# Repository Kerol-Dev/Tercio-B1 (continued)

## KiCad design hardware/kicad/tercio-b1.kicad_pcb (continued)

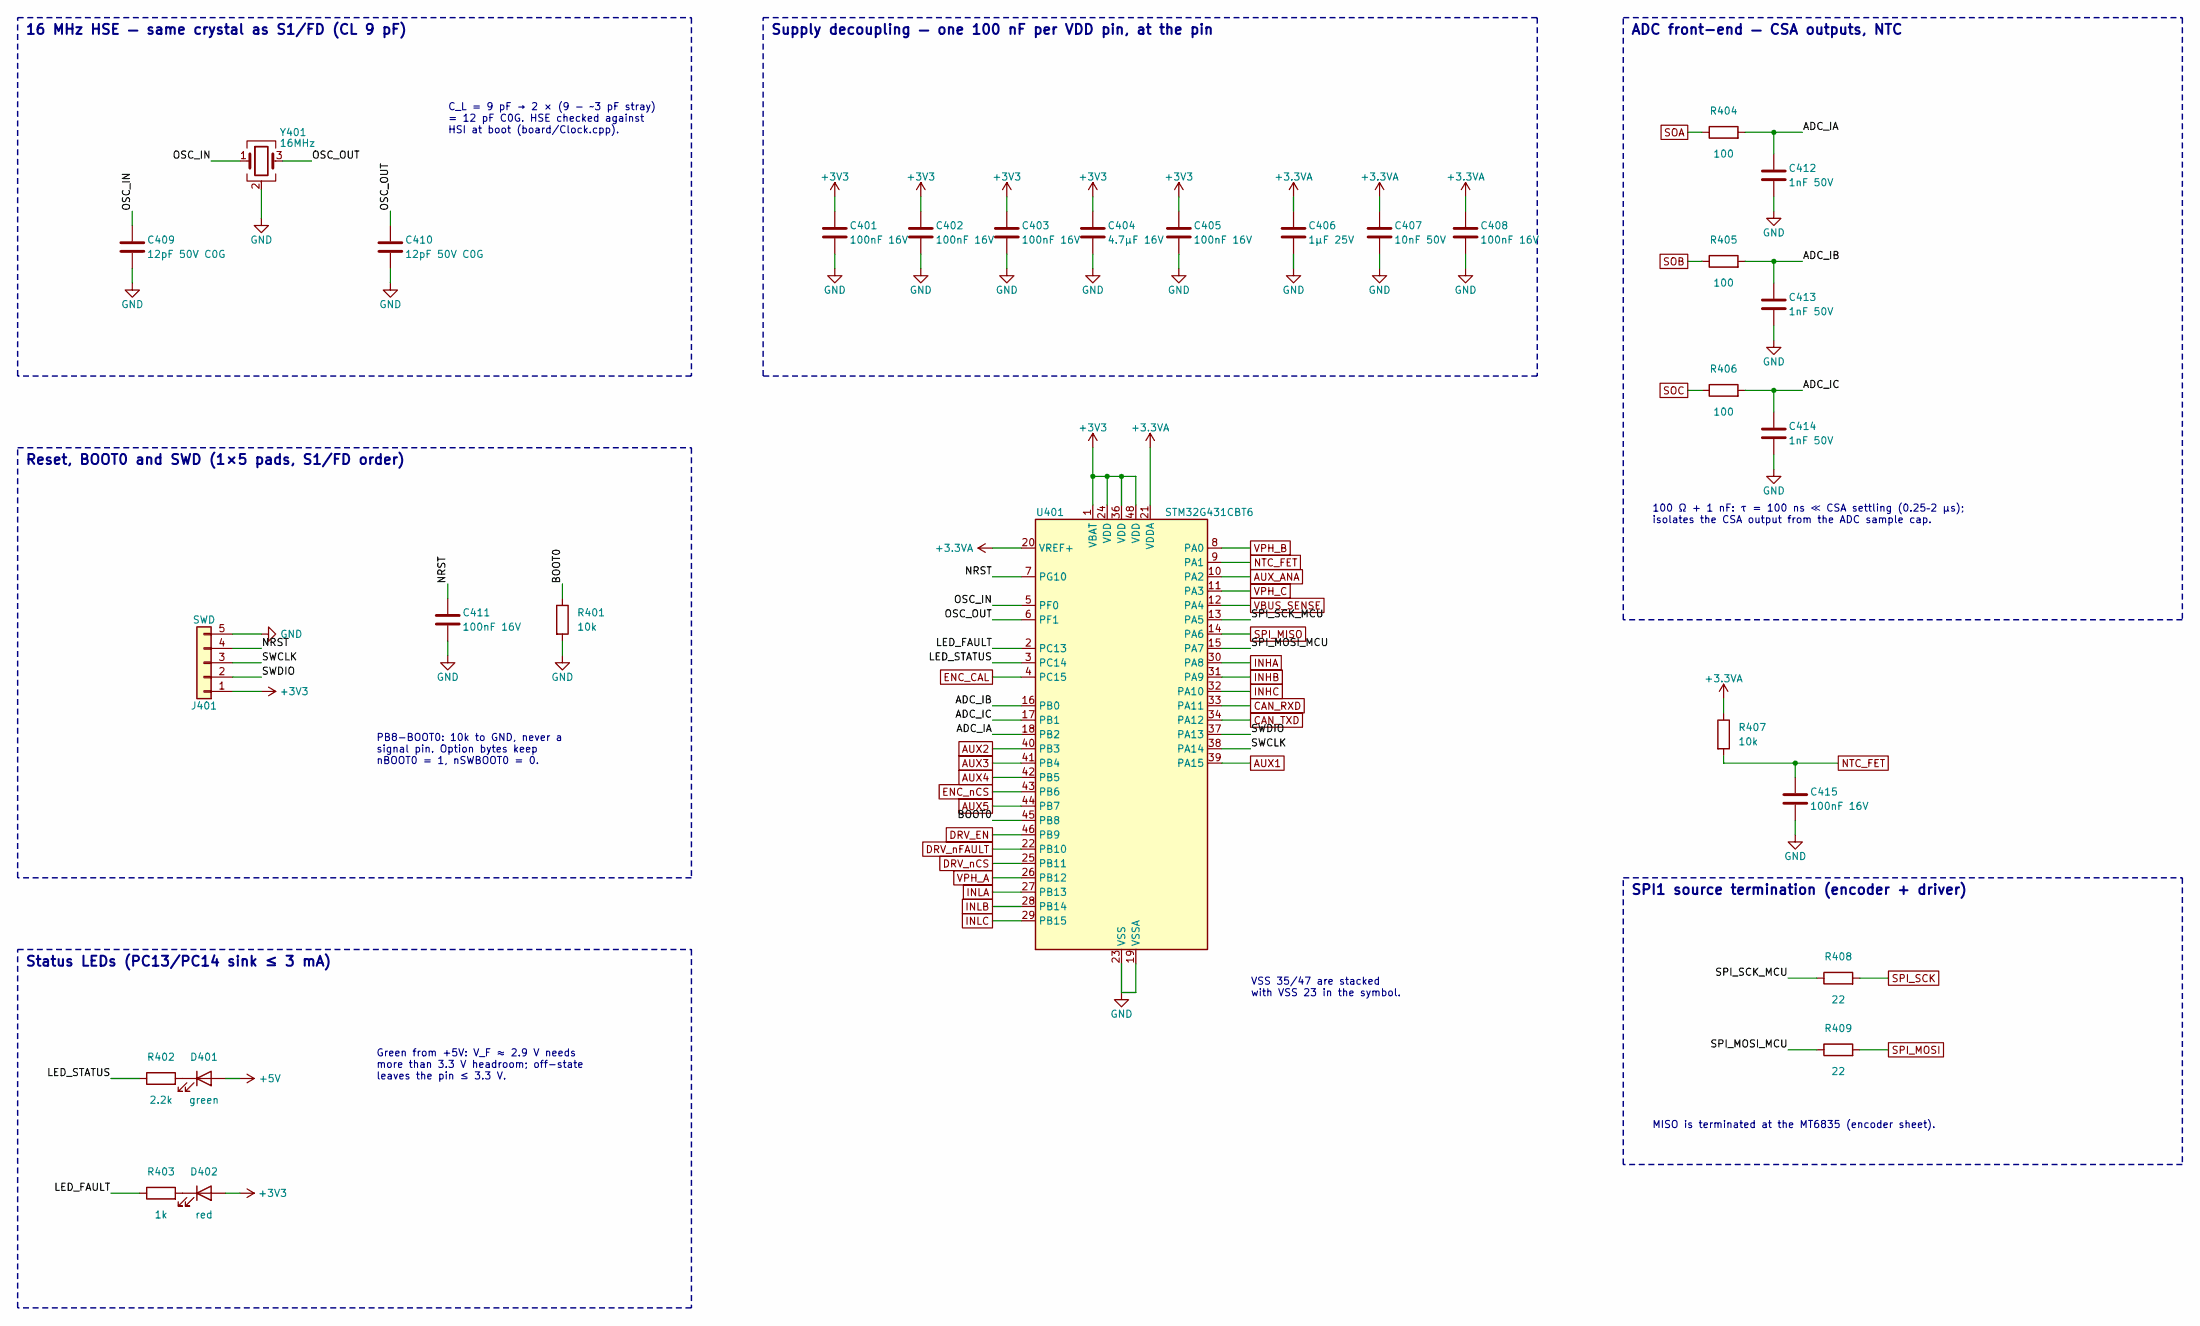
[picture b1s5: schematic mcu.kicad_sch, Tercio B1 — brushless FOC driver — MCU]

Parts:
C401, C402, C403, C405, C408, C411, C415: 100nF 16V; C_0402_1005Metric; LCSC C1525
C404: 4.7µF 16V; C_0603_1608Metric; LCSC C19666
C406: 1µF 25V; C_0402_1005Metric; LCSC C52923
C407: 10nF 50V; C_0402_1005Metric; LCSC C15195
C409, C410: 12pF 50V C0G; C_0402_1005Metric; LCSC C1547
C412, C413, C414: 1nF 50V; C_0402_1005Metric; LCSC C1523
D401: green; LED_0805_2012Metric; MPN KT-0805G; LCSC C2297
D402: red; LED_0603_1608Metric; MPN KT-0603R; LCSC C2286
J401: SWD; SWD_Pads_1x05_P2.54mm
R401, R407: 10k; R_0402_1005Metric; LCSC C25744
R402: 2.2k; R_0402_1005Metric; LCSC C25879
R403: 1k; R_0402_1005Metric; LCSC C11702
R404, R405, R406: 100; R_0402_1005Metric; LCSC C25076
R408, R409: 22; R_0402_1005Metric; LCSC C25092
U401: STM32G431CBT6; LQFP-48_7x7mm_P0.5mm; MPN STM32G431CBT6; LCSC C529355
Y401: 16MHz; Crystal_SMD_3225-4Pin_3.2x2.5mm; MPN X322516MLB4SI; LCSC C13738

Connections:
+3.3VA: C406.1, C407.1, C408.1, R407.1, U401.20 (VREF+), U401.21 (VDDA); also elsewhere on the board
+3V3: C401.1, C402.1, C403.1, C404.1, C405.1, D402.2 (A), J401.1, U401.1 (VBAT), U401.24 (VDD), U401.36 (VDD), U401.48 (VDD); also elsewhere on the board
+5V: D401.2 (A); also elsewhere on the board
/MCU/ADC_IA: C412.1, R404.2, U401.18 (PB2)
/MCU/ADC_IB: C413.1, R405.2, U401.16 (PB0)
/MCU/ADC_IC: C414.1, R406.2, U401.17 (PB1)
/MCU/BOOT0: R401.1, U401.45 (PB8)
/MCU/LED_FAULT: R403.1, U401.2 (PC13)
/MCU/LED_STATUS: R402.1, U401.3 (PC14)
/MCU/NRST: C411.1, J401.4, U401.7 (PG10)
/MCU/OSC_IN: C409.1, U401.5 (PF0), Y401.1
/MCU/OSC_OUT: C410.1, U401.6 (PF1), Y401.3
/MCU/SPI_MOSI_MCU: R409.1, U401.15 (PA7)
/MCU/SPI_SCK_MCU: R408.1, U401.13 (PA5)
/MCU/SWCLK: J401.3, U401.38 (PA14)
/MCU/SWDIO: J401.2, U401.37 (PA13)
AUX1: U401.39 (PA15); also elsewhere on the board
AUX2: U401.40 (PB3); also elsewhere on the board
AUX3: U401.41 (PB4); also elsewhere on the board
AUX4: U401.42 (PB5); also elsewhere on the board
AUX5: U401.44 (PB7); also elsewhere on the board
AUX_ANA: U401.10 (PA2); also elsewhere on the board
CAN_RXD: U401.33 (PA11); also elsewhere on the board
CAN_TXD: U401.34 (PA12); also elsewhere on the board
DRV_EN: U401.46 (PB9); also elsewhere on the board
DRV_nCS: U401.25 (PB11); also elsewhere on the board
DRV_nFAULT: U401.22 (PB10); also elsewhere on the board
ENC_CAL: U401.4 (PC15); also elsewhere on the board
ENC_nCS: U401.43 (PB6); also elsewhere on the board
GND: C401.2, C402.2, C403.2, C404.2, C405.2, C406.2, C407.2, C408.2, C409.2, C410.2, C411.2, C412.2, C413.2, C414.2, C415.2, J401.5, R401.2, U401.19 (VSSA), U401.23 (VSS), U401.35 (VSS), U401.47 (VSS), Y401.2 (G), Y401.4 (G); also elsewhere on the board
INHA: U401.30 (PA8); also elsewhere on the board
INHB: U401.31 (PA9); also elsewhere on the board
INHC: U401.32 (PA10); also elsewhere on the board
INLA: U401.27 (PB13); also elsewhere on the board
INLB: U401.28 (PB14); also elsewhere on the board
INLC: U401.29 (PB15); also elsewhere on the board
NTC_FET: C415.1, R407.2, U401.9 (PA1); also elsewhere on the board
unnamed: D401.1 (K), R402.2
unnamed: D402.1 (K), R403.2
SOA: R404.1; also elsewhere on the board
SOB: R405.1; also elsewhere on the board
SOC: R406.1; also elsewhere on the board
SPI_MISO: U401.14 (PA6); also elsewhere on the board
SPI_MOSI: R409.2; also elsewhere on the board
SPI_SCK: R408.2; also elsewhere on the board
VBUS_SENSE: U401.12 (PA4); also elsewhere on the board
VPH_A: U401.26 (PB12); also elsewhere on the board
VPH_B: U401.8 (PA0); also elsewhere on the board
VPH_C: U401.11 (PA3); also elsewhere on the board

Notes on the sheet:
Supply decoupling — one 100 nF per VDD pin, at the pin
16 MHz HSE — same crystal as S1/FD (CL 9 pF)
Reset, BOOT0 and SWD (1×5 pads, S1/FD order)
Status LEDs (PC13/PC14 sink ≤ 3 mA)
ADC front-end — CSA outputs, NTC
SPI1 source termination (encoder + driver)
VSS 35/47 are stacked with VSS 23 in the symbol.
C_L = 9 pF → 2 × (9 − ~3 pF stray) = 12 pF C0G. HSE checked against HSI at boot (board/Clock.cpp).
PB8-BOOT0: 10k to GND, never a signal pin. Option bytes keep nBOOT0 = 1, nSWBOOT0 = 0.
Green from +5V: V_F ≈ 2.9 V needs more than 3.3 V headroom; off-state leaves the pin ≤ 3.3 V.
100 Ω + 1 nF: τ = 100 ns ≪ CSA settling (0.25–2 µs); isolates the CSA output from the ADC sample cap.
MISO is terminated at the MT6835 (encoder sheet).

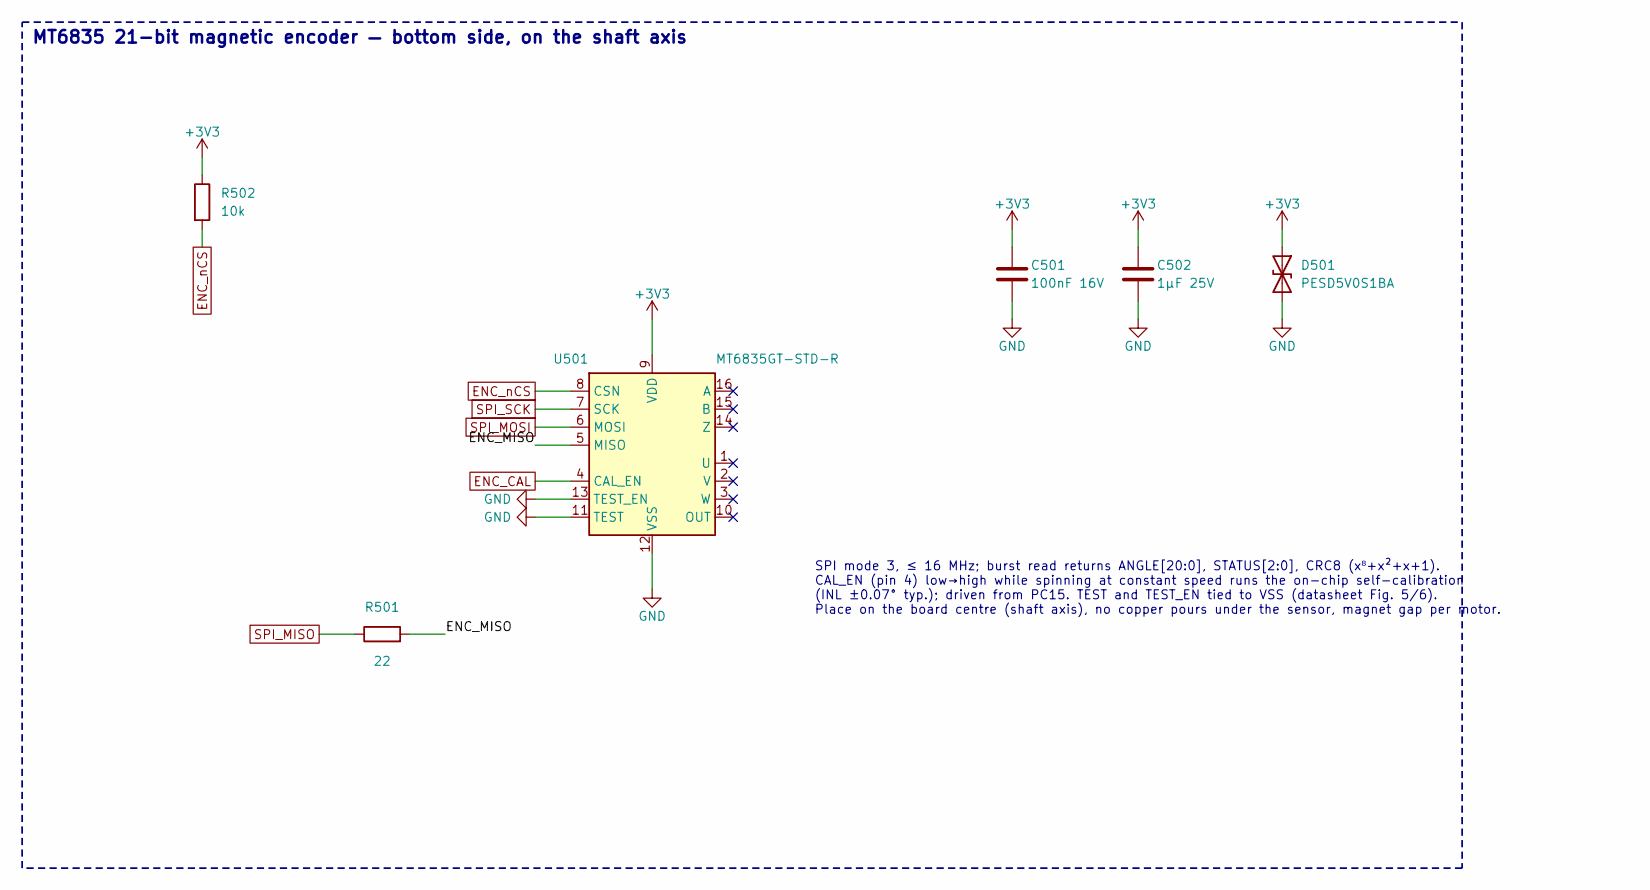
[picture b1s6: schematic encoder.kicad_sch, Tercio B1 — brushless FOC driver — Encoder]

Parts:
C501: 100nF 16V; C_0402_1005Metric; LCSC C1525
C502: 1µF 25V; C_0402_1005Metric; LCSC C52923
D501: PESD5V0S1BA; D_SOD-323; MPN PESD5V0S1BA; LCSC C2827694
R501: 22; R_0402_1005Metric; LCSC C25092
R502: 10k; R_0402_1005Metric; LCSC C25744
U501: MT6835GT-STD-R; TSSOP-16_4.4x5mm_P0.65mm; MPN MT6835GT-STD-R; LCSC C2932578

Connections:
+3V3: C501.1, C502.1, D501.1 (A1), R502.1, U501.9 (VDD); also elsewhere on the board
/Encoder/ENC_MISO: R501.2, U501.5 (MISO)
ENC_CAL: U501.4 (CAL_EN); also elsewhere on the board
ENC_nCS: R502.2, U501.8 (CSN); also elsewhere on the board
GND: C501.2, C502.2, D501.2 (A2), U501.11 (TEST), U501.12 (VSS), U501.13 (TEST_EN); also elsewhere on the board
SPI_MISO: R501.1; also elsewhere on the board
SPI_MOSI: U501.6 (MOSI); also elsewhere on the board
SPI_SCK: U501.7 (SCK); also elsewhere on the board

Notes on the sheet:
MT6835 21-bit magnetic encoder — bottom side, on the shaft axis
SPI mode 3, ≤ 16 MHz; burst read returns ANGLE[20:0], STATUS[2:0], CRC8 (x⁸+x²+x+1). CAL_EN (pin 4) low→high while spinning at constant speed runs the on-chip self-calibration (INL ±0.07° typ.); driven from PC15. TEST and TEST_EN tied to VSS (datasheet Fig. 5/6). Place on the board centre (shaft ax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

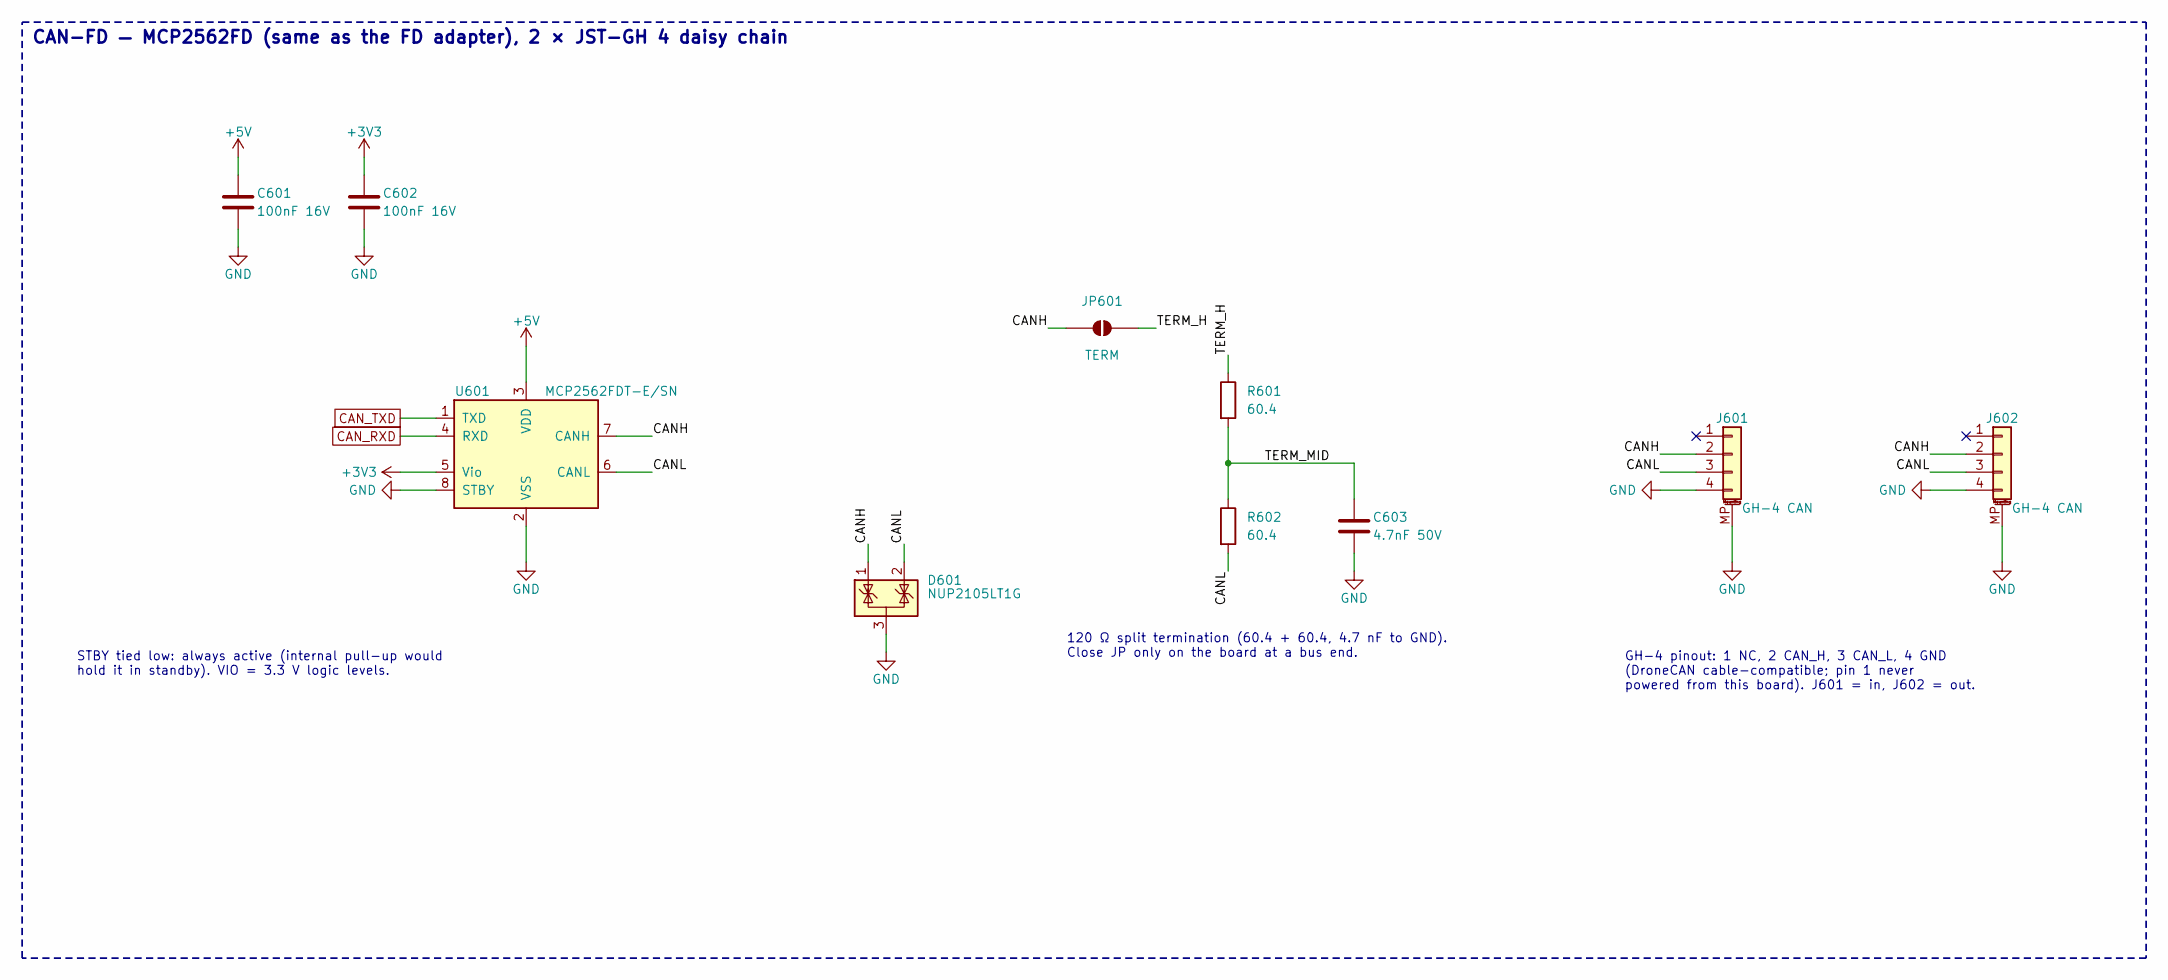
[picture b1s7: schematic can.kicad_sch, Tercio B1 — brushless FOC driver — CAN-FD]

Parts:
C601, C602: 100nF 16V; C_0402_1005Metric; LCSC C1525
C603: 4.7nF 50V; C_0402_1005Metric; LCSC C1538
D601: NUP2105LT1G; SOT-23; MPN NUP2105LT1G; LCSC C14486
J601, J602: GH-4 CAN; JST_GH_SM04B-GHS-TB_1x04-1MP_P1.25mm_Horizontal; MPN SM04B-GHS-TB(LF)(SN); LCSC C189895
JP601: TERM; SolderJumper-2_P1.3mm_Open_RoundedPad1.0x1.5mm
R601, R602: 60.4; R_0402_1005Metric; LCSC C137954
U601: MCP2562FDT-E/SN; SOIC-8_3.9x4.9mm_P1.27mm; MPN MCP2562FDT-E/SN; LCSC C511335

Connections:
+3V3: C602.1, U601.5 (Vio); also elsewhere on the board
+5V: C601.1, U601.3 (VDD); also elsewhere on the board
/CAN-FD/CANH: D601.1 (K), J601.2, J602.2, JP601.1 (A), U601.7 (CANH)
/CAN-FD/CANL: D601.2 (K), J601.3, J602.3, R602.2, U601.6 (CANL)
/CAN-FD/TERM_H: JP601.2 (B), R601.1
/CAN-FD/TERM_MID: C603.1, R601.2, R602.1
CAN_RXD: U601.4 (RXD); also elsewhere on the board
CAN_TXD: U601.1 (TXD); also elsewhere on the board
GND: C601.2, C602.2, C603.2, D601.3 (A), J601.4, J601.MP (MountPin), J602.4, J602.MP (MountPin), U601.2 (VSS), U601.8 (STBY); also elsewhere on the board

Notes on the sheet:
CAN-FD — MCP2562FD (same as the FD adapter), 2 × JST-GH 4 daisy chain
STBY tied low: always active (internal pull-up would hold it in standby). VIO = 3.3 V logic levels.
120 Ω split termination (60.4 + 60.4, 4.7 nF to GND). Close JP only on the board at a bus end.
GH-4 pinout: 1 NC, 2 CAN_H, 3 CAN_L, 4 GND (DroneCAN cable-compatible; pin 1 never powered from this board). J601 = in, J602 = out.

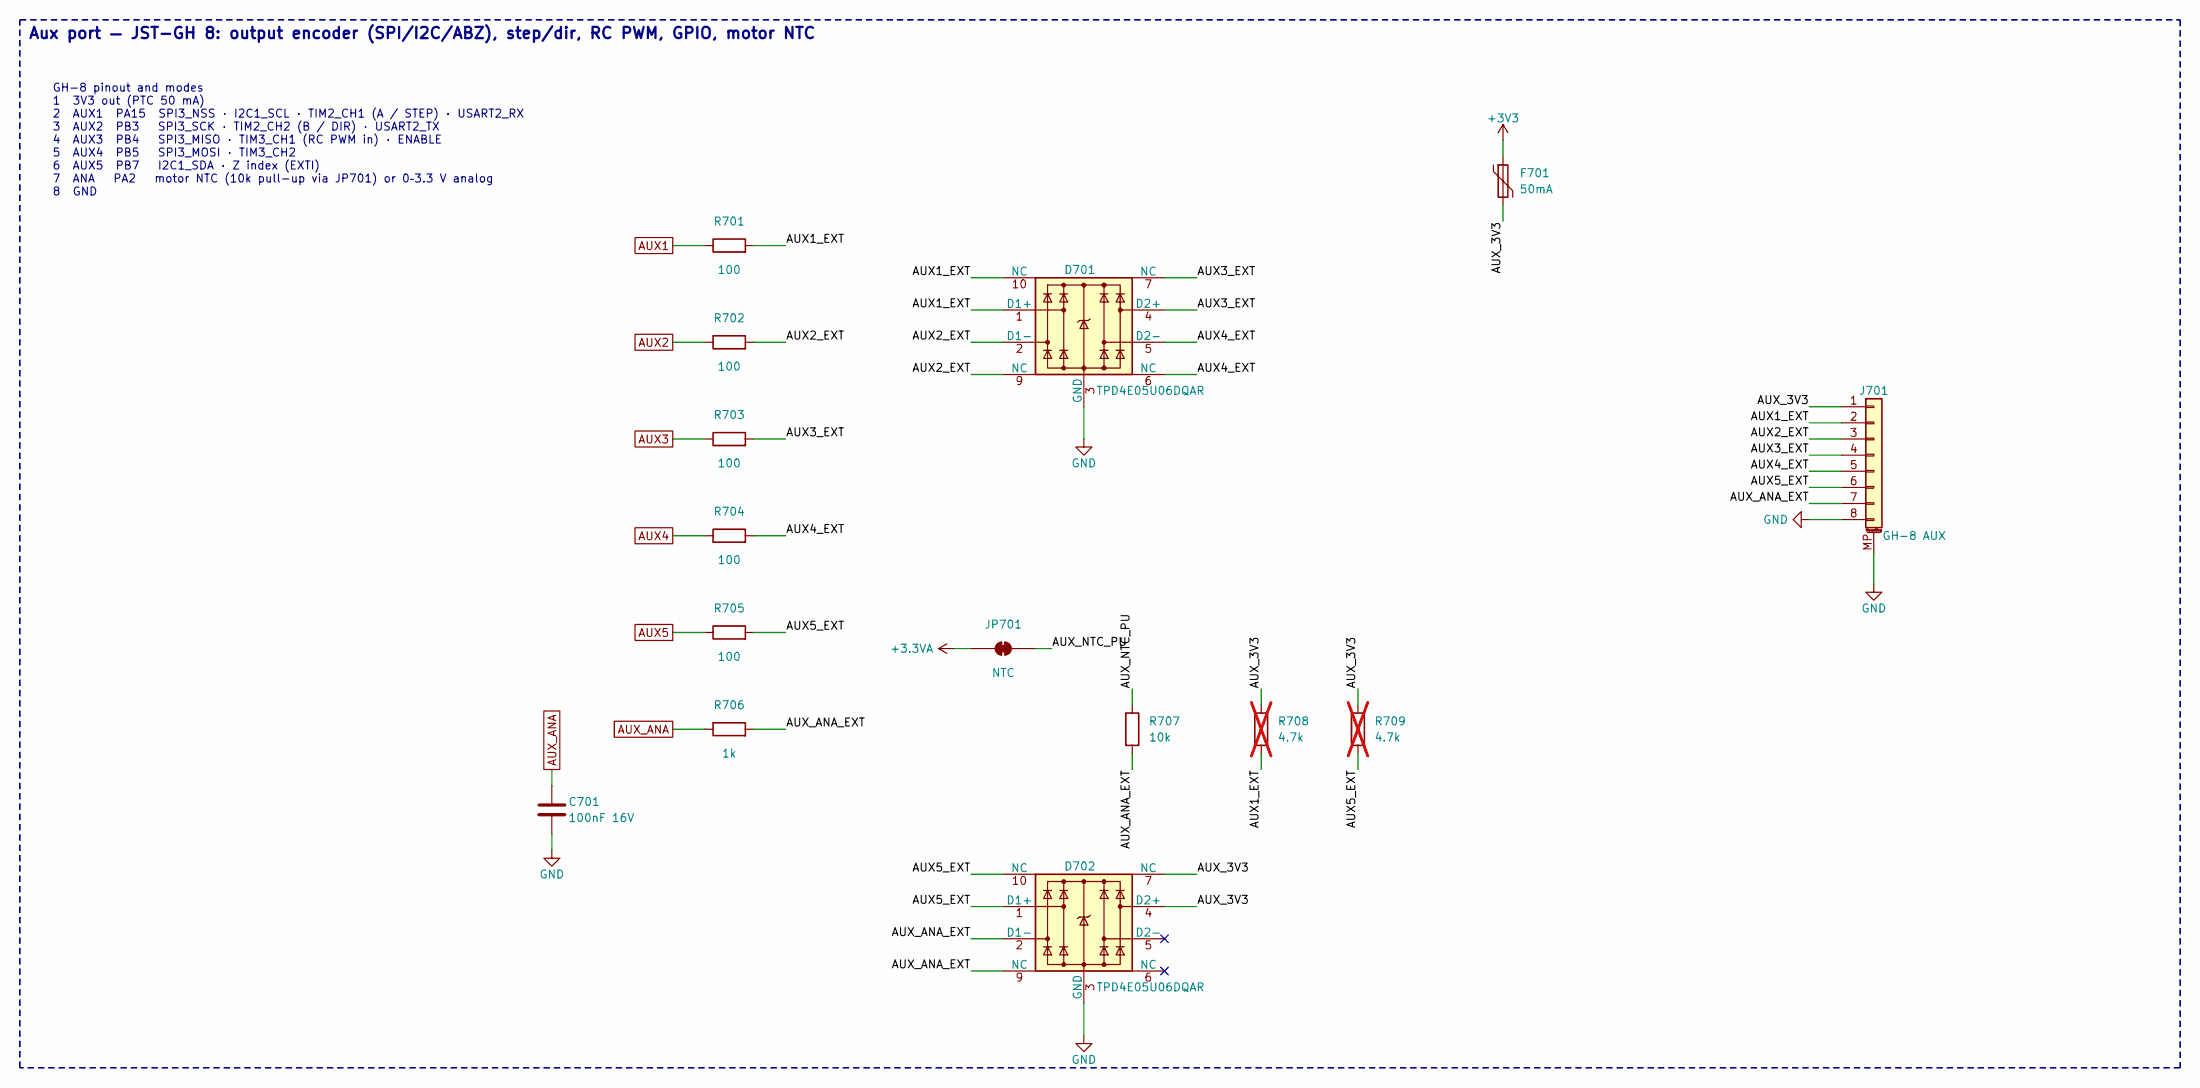
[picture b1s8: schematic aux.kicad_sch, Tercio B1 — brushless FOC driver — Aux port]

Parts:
C701: 100nF 16V; C_0402_1005Metric; LCSC C1525
D701, D702: TPD4E05U06DQAR; USON-10_2.5x1.0mm_P0.5mm; MPN TPD4E05U06DQAR; LCSC C138714
F701: 50mA; Fuse_0603_1608Metric; MPN 0603L005/24AR; LCSC C7472511
J701: GH-8 AUX; JST_GH_SM08B-GHS-TB_1x08-1MP_P1.25mm_Horizontal; MPN SH-SM08B-GHS-TB(LF)(SN); LCSC C42376901
JP701: NTC; SolderJumper-2_P1.3mm_Bridged_RoundedPad1.0x1.5mm
R701, R702, R703, R704, R705: 100; R_0402_1005Metric; LCSC C25076
R706: 1k; R_0402_1005Metric; LCSC C11702
R707: 10k; R_0402_1005Metric; LCSC C25744
R708, R709: 4.7k; R_0402_1005Metric; not fitted

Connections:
+3.3VA: JP701.1 (A); also elsewhere on the board
+3V3: F701.1; also elsewhere on the board
/Aux port/AUX1_EXT: D701.1 (D1+), D701.10 (NC), J701.2, R701.2, R708.2
/Aux port/AUX2_EXT: D701.2 (D1-), D701.9 (NC), J701.3, R702.2
/Aux port/AUX3_EXT: D701.4 (D2+), D701.7 (NC), J701.4, R703.2
/Aux port/AUX4_EXT: D701.5 (D2-), D701.6 (NC), J701.5, R704.2
/Aux port/AUX5_EXT: D702.1 (D1+), D702.10 (NC), J701.6, R705.2, R709.2
/Aux port/AUX_3V3: D702.4 (D2+), D702.7 (NC), F701.2, J701.1, R708.1, R709.1
/Aux port/AUX_ANA_EXT: D702.2 (D1-), D702.9 (NC), J701.7, R706.2, R707.2
/Aux port/AUX_NTC_PU: JP701.2 (B), R707.1
AUX1: R701.1; also elsewhere on the board
AUX2: R702.1; also elsewhere on the board
AUX3: R703.1; also elsewhere on the board
AUX4: R704.1; also elsewhere on the board
AUX5: R705.1; also elsewhere on the board
AUX_ANA: C701.1, R706.1; also elsewhere on the board
GND: C701.2, D701.3 (GND), D701.8 (GND), D702.3 (GND), D702.8 (GND), J701.8, J701.MP (MountPin); also elsewhere on the board

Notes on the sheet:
Aux port — JST-GH 8: output encoder (SPI/I2C/ABZ), step/dir, RC PWM, GPIO, motor NTC
GH-8 pinout and modes 1 3V3 out (PTC 50 mA) 2 AUX1 PA15 SPI3_NSS · I2C1_SCL · TIM2_CH1 (A / STEP) · USART2_RX 3 AUX2 PB3 SPI3_SCK · TIM2_CH2 (B / DIR) · USART2_TX 4 AUX3 PB4 SPI3_MISO · TIM3_CH1 (RC PWM in) · ENABLE 5 AUX4 PB5 SPI3_MOSI · TIM3_CH2 6 AUX5 PB7 I2C1_SDA · Z index (EXTI) 7 ANA PA2 moto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

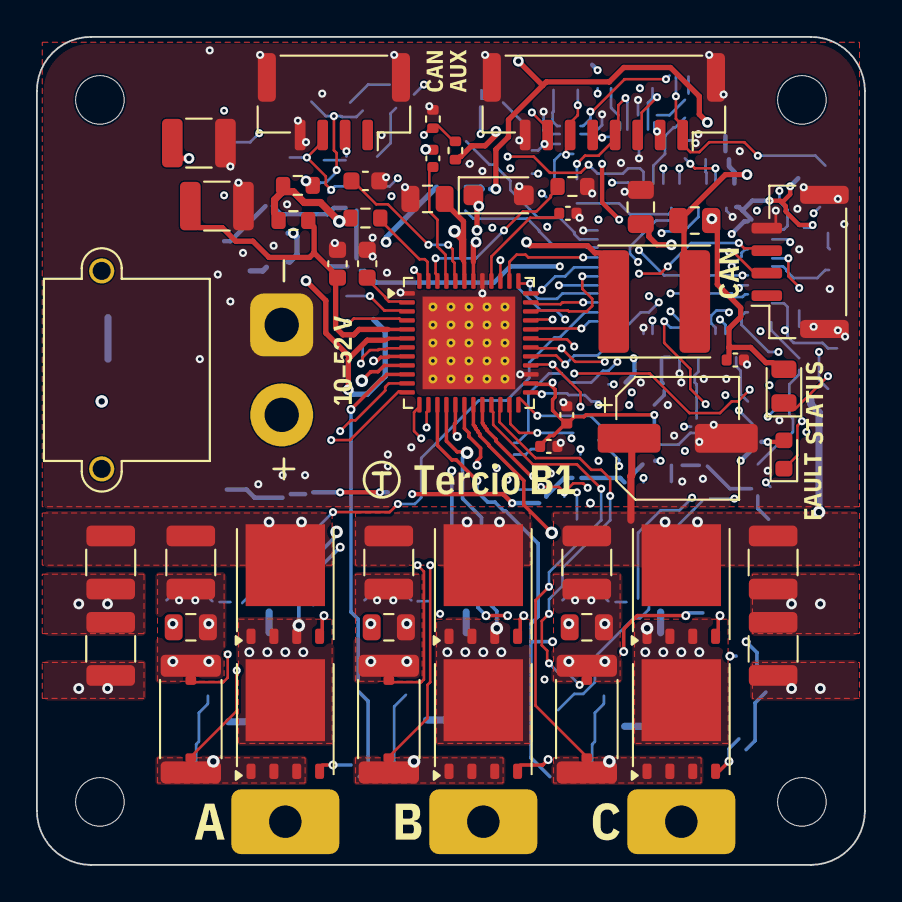
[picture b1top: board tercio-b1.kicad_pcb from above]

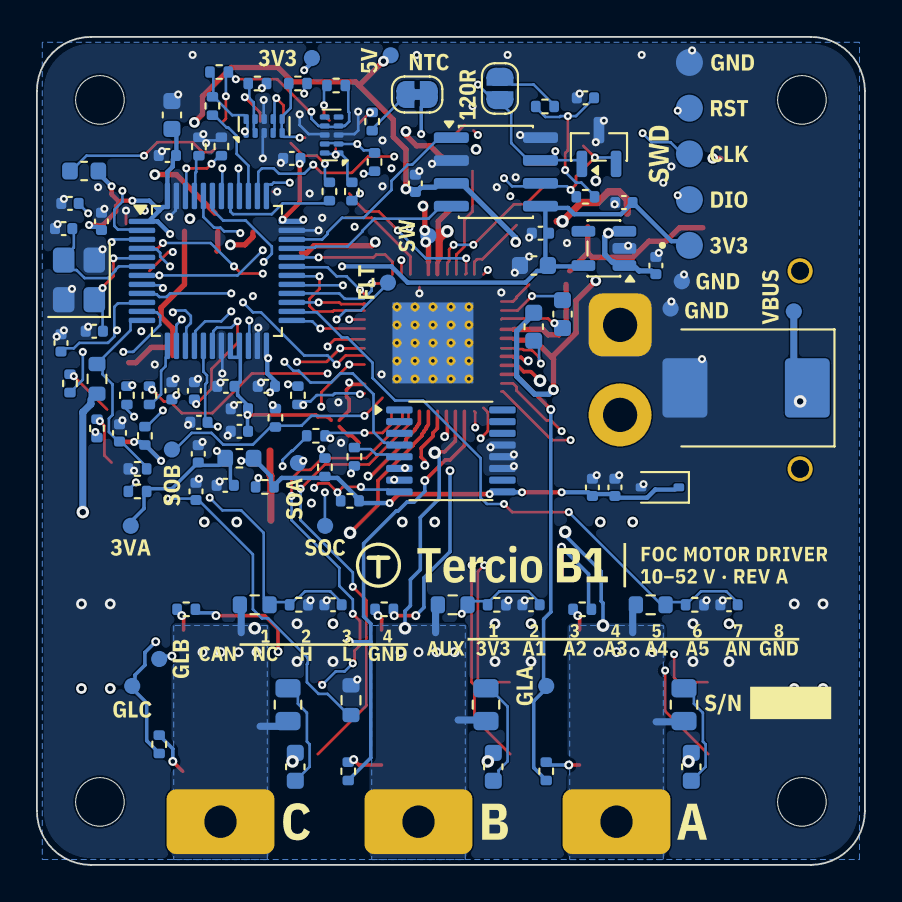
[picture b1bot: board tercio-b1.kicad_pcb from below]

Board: 6 copper layers, 46.0 x 46.0 mm, 163 parts (108 on the bottom side), 104 nets.

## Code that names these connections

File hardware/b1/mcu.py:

"""Sheet 5 — STM32G431CBT6: supplies, clock, reset/boot, SWD, LEDs, ADC front-end, SPI source termination."""
from gen.catalog import FP, PART, Kit
from gen.model import NC

from .layout import G, rc_lowpass, vert

# Pin map: docs/04-architecture.md §4.2 (data/pinmap-g431cbt6.csv)
PINMAP = {
    "PC13": "LED_FAULT", "PC14": "LED_STATUS", "PC15": "ENC_CAL",
    "PF0": "OSC_IN", "PF1": "OSC_OUT", "PG10": "NRST",
    "PA0": "VPH_B", "PA1": "NTC_FET", "PA2": "AUX_ANA", "PA3": "VPH_C", "PA4": "VBUS_SENSE",
    "PA5": "SPI_SCK_MCU", "PA6": "SPI_MISO", "PA7": "SPI_MOSI_MCU",
    "PB0": "ADC_IB", "PB1": "ADC_IC", "PB2": "ADC_IA",
    "PB10": "DRV_nFAULT", "PB11": "DRV_nCS", "PB12": "VPH_A",
    "PB13": "INLA", "PB14": "INLB", "PB15": "INLC",
    "PA8": "INHA", "PA9": "INHB", "PA10": "INHC",
    "PA11": "CAN_RXD", "PA12": "CAN_TXD", "PA13": "SWDIO", "PA14": "SWCLK",
    "PA15": "AUX1", "PB3": "AUX2", "PB4": "AUX3", "PB5": "AUX4", "PB6": "ENC_nCS", "PB7": "AUX5",
    "PB8": "BOOT0", "PB9": "DRV_EN",
}


def build(sch):
    sh = sch.sheet("mcu.kicad_sch", "MCU", page=5, ref_base=400)
    k = Kit(sh)

    X, Y = 215.9, 152.4
    u = sh.part("MCU_ST_STM32G4:STM32G431CBTx", "STM32G431CBT6", (X, Y), fp=FP["LQFP48"],
                lcsc=PART["STM32G431CBT6"], mpn="STM32G431CBT6")
    for pin, net in PINMAP.items():
        u[pin] = net
    u["VREF+"] = "+3.3VA"
    u.stub = 5.08
    # supplies: VBAT + 3 × VDD on one +3V3 bus, VDDA alone, VSS/VSSA joined
    ytop = Y - 40.64
    pts = [u.wire_to(n, "+3V3") for n in ("1", "24", "36", "48")]
    for x, y in pts:
        sh.wire((x, y), (x, ytop - 5.08))
    sh.wire((pts[0][0], ytop - 5.08), (pts[-1][0], ytop - 5.08))
    for x, _ in pts[1:-1]:
        sh.junction(x, ytop - 5.08)
    sh.wire((pts[0][0], ytop - 5.08), (pts[0][0], ytop - 10.16))
    sh.junction(pts[0][0], ytop - 5.08)
    sh.power("+3V3", pts[0][0], ytop - 10.16, 90)
    vdda = u.wire_to("VDDA", "+3.3VA")
    sh.wire(vdda, (vdda[0], ytop - 10.16))
    sh.power("+3.3VA", vdda[0], ytop - 10.16, 90)
    vss, vssa = u.wire_to("23", "GND"), u.wire_to("VSSA", "GND")
    ybot = Y + 40.64 + 5.08
    sh.wire(vss, (vss[0], ybot)); sh.wire(vssa, (vssa[0], ybot)); sh.wire((vss[0], ybot), (vssa[0], ybot))
    sh.power("GND", vss[0], ybot, 270)
    sh.note(X + 22.86, Y + 43.18, "VSS 35/47 are stacked\nwith VSS 23 in the symbol.", size=1.27)

    # ---- decoupling ------------------------------------------------------------------------------------
    sh.box(152.4, 25.4, 289.56, 88.9, "Supply decoupling — one 100 nF per VDD pin, at the pin")
    y = 63.5
    for i in range(3):
        vert(k.C("100n", (165.1 + i * 15.24, y)), "+3V3", "GND")
    vert(k.C("4.7u", (210.82, y), pkg="0603"), "+3V3", "GND")
    vert(k.C("100n", (226.06, y)), "+3V3", "GND")                     # VBAT
    vert(k.C("1u", (246.38, y)), "+3.3VA", "GND")                     # VDDA / VREF+
    vert(k.C("10n", (261.62, y)), "+3.3VA", "GND")
    vert(k.C("100n", (276.86, y)), "+3.3VA", "GND")

    # ---- clock ---------------------------------------------------------------------------------------------
    sh.box(20.32, 25.4, 139.7, 88.9, "16 MHz HSE — same crystal as S1/FD (CL 9 pF)")
    xt = sh.part("Device:Crystal_GND24", "16MHz", (63.5, 50.8), fp=FP["XTAL3225"], lcsc=PART["X322516MLB4SI"],
                 mpn="X322516MLB4SI", ref="Y")
    xt[1] = "OSC_IN"; xt[3] = "OSC_OUT"; xt[2] = "GND"
    xt.stub = 5.08
    vert(k.C("12p", (40.64, 66.04)), "OSC_IN", "GND")
    vert(k.C("12p", (86.36, 66.04)), "OSC_OUT", "GND")
    sh.note(96.52, 40.64, "C_L = 9 pF → 2 × (9 − ~3 pF stray)\n= 12 pF C0G. HSE checked against\nHSI at boot (board/Clock.cpp).", size=1.27)

    # ---- reset, boot, SWD ------------------------------------------------------------------------------------------
    sh.box(20.32, 101.6, 139.7, 177.8, "Reset, BOOT0 and SWD (1×5 pads, S1/FD order)")
    j = sh.part("Connector_Generic:Conn_01x05", "SWD", (53.34, 139.7), rot=180, fp=FP["SWDPADS"], ref="J")
    j.in_bom = False  # bare pads on the bottom: pogo adapter or soldered wires
    j[1] = "+3V3"; j[2] = "SWDIO"; j[3] = "SWCLK"; j[4] = "NRST"; j[5] = "GND"
    j.stub = 5.08
    vert(k.C("100n", (96.52, 132.08)), "NRST", "GND")                  # ST: 100 nF on NRST (missing on S1)
    vert(k.R("10k", (116.84, 132.08)), "BOOT0", "GND")                 # BOOT0 pull-down (S1/FD lesson)
    sh.note(83.82, 152.4, "PB8-BOOT0: 10k to GND, never a\nsignal pin. Option bytes keep\nnBOOT0 = 1, nSWBOOT0 = 0.", size=1.27)

    # ---- LEDs ---------------------------------------------------------------------------------------------------------
    sh.box(20.32, 190.5, 139.7, 254.0, "Status LEDs (PC13/PC14 sink ≤ 3 mA)")
    for i, (net, color, part, supply, r) in enumerate((
            ("LED_STATUS", "green", "KT-0805G", "+5V", "2.2k"),
            ("LED_FAULT", "red", "KT-0603R", "+3V3", "1k"))):
        y = 213.36 + i * 20.32
        rr = k.R(r, (45.72, y), rot=90)
        rr[1] = net
        rr.stub = 5.08
        kpt = rr.wire_to(2, f"{net}_K")
        led = sh.part("Device:LED", color, (kpt[0] + 3.81, y), fp=FP["LED0805" if color == "green" else "LED0603"],
                      lcsc=PART[part], mpn=part, ref="D")
        led.wire_to("K", f"{net}_K")
        led["A"] = supply
    sh.note(83.82, 208.28, "Green from +5V: V_F ≈ 2.9 V needs\nmore than 3.3 V headroom; off-state\nleaves the pin ≤ 3.3 V.", size=1.27)

    # ---- ADC front-end -----------------------------------------------------------------------------------------------
    sh.box(304.8, 25.4, 403.86, 132.08, "ADC front-end — CSA outputs, NTC")
    for i, ph in enumerate("ABC"):
        rc_lowpass(k, 322.58, 45.72 + i * 22.86, f"SO{ph}", f"ADC_I{ph}", "100", "1n")
    sh.note(309.88, 111.76, "100 Ω + 1 nF: τ = 100 ns ≪ CSA settling (0.25–2 µs);\nisolates the CSA output from the ADC sample cap.", size=1.27)
    yn = 152.4
    rn = k.R("10k", (322.58, yn))
    rn[1] = "+3.3VA"
    p = rn.wire_to(2, "NTC_FET")
    cn = k.C("100n", (335.28, yn + 11.43))
    t = cn.wire_to(1, "NTC_FET")
    cn[2] = "GND"
    sh.wire(p, (322.58, yn + 5.08)); sh.wire((322.58, yn + 5.08), (335.28, yn + 5.08), t)
    sh.wire((335.28, yn + 5.08), (342.9, yn + 5.08)); sh.junction(335.28, yn + 5.08)
    sh.label("NTC_FET", 342.9, yn + 5.08, 0)

    # ---- SPI source termination --------------------------------------------------------------------------------------
    sh.box(304.8, 177.8, 403.86, 228.6, "SPI1 source termination (encoder + driver)")
    for i, (a, b) in enumerate((("SPI_SCK_MCU", "SPI_SCK"), ("SPI_MOSI_MCU", "SPI_MOSI"))):
        r = k.R("22", (342.9, 195.58 + i * 12.7), rot=90)
        r[1] = a; r[2] = b
        r.stub = 5.08
    sh.note(309.88, 220.98, "MISO is terminated at the MT6835 (encoder sheet).", size=1.27)
    return sh

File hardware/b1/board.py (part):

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    # ---- top: driver ------------------------------------------------------------------------------
    p.place("U201", 1.0, -6.0)                    # thermal vias end 1.2 mm from the encoder (bottom, centre);
    #                                               x leaves a 3.7 mm band between the XT30 and the left pins
    # buck, above the DRV's top pins (48 FB … 43 VIN, 42 SW, 41 GND, 40 DVDD, 39–37 INx at 0.5 mm):
    # the catch diode lies across the top with its cathode straight above SW (pin 42), its anode
    # clear of the INx/DVDD fan; the VIN cap sits up-left where VIN turns after the left fan
    p.place("D201", 2.65, -14.2)                  # SOD-123FL, K over pin 42, A over pins 37–38
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    p.keepout_rect(-7.2, -9.3, -3.35, -5.55, sides=("T",), name="supply fan")   # pins 2–7, to C207/C202 and vias
    # DRV supply caps, by hand: the 3.2 mm band between the XT30 courtyard and the left pins, above the fan
    # the charge-pump caps (tens of mA) go under the band on the bottom, through vias, so pins 2–7
    # can fan out on top to the VGLS and VM caps; the VCP and flying caps sit right below their pins
    p.place("C206", -4.6, -6.9, rot=90, side="B")   # VCP (high-side gate supply), pins 6–7
    p.place("C205", -6.2, -7.6, rot=90, side="B")   # charge-pump flying cap, pins 3–4
    p.place("C207", -4.65, -10.4, rot=90)         # VGLS (low-side gate supply), pin 2
    p.place("C202", -6.3, -10.4, rot=90)          # VM 100 nF (0603), pin 5

    # ---- top: connectors -------------------------------------------------------------------------------
    # right-angle GH: cable entry is on the mounting-tab side (+y in the footprint) → face it off the board.
    # The aux connector sits top right, straight above the MCU's aux pins (PA15, PB3–PB7 face up);
    # CAN in takes the top left, CAN out the right edge, the transceiver between them
    p.place("J701", 8.5, -19.4, rot=180)          # aux GH-8, entry at the top edge
    p.place("J601", -6.5, -19.4, rot=180)         # CAN GH-4 (in), entry at the top edge
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    p.place("D402", 18.5, 0.2, rot=90)

    # ---- bottom: sensor, MCU, CAN ----------------------------------------------------------------------
    # The MCU sits beside the driver, under its right-hand pins: rotated 180° its PB11–PA10 side (DRV_nCS,
    # the six PWM inputs, CAN) faces the DRV's pins 32–39 across a 3 mm via lane, the aux pins face the
    # aux connector, PB0–PB2 (currents) and SPI face the encoder and the DRV's SO / SPI corner, the
    # crystal and the slow analog inputs face the free right edge. The encoder is turned 180° so its
    # SPI pins face the MCU too (its angle offset is calibrated anyway).
    p.place("U501", 0.0, 0.0, rot=180, side="B")  # MT6835 exactly on the shaft axis
    p.place("U401", *MCU, rot=180, side="B")
    p.place("U601", -2.5, -15.5, rot=180, side="B")  # TXD/RXD face the MCU's PA11/PA12, CANH/L face J601
    p.keepout_rect(4.2, -13.4, 7.9, -1.6, sides=("B",), name="drv link vias")   # DRV pins 23–39 → MCU
    # phase A's gate loop leaves the DRV's left pins and drops through here to the bottom / In3
    p.keepout_rect(-7.2, -5.55, -5.1, 3.3, sides=("B",), name="gate A vias")
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        ("R501", ("U501", "5"), B, None), ("R502", ("U501", "8"), B, (2.86, 6.0)),
        ("C501", ("U501", "9"), B, (-6.0, 2.0)), ("C502", ("U501", "9"), B, (-6.0, 2.0)),
        ("D501", ("U501", "9"), B, (-6.0, 2.0)),
        # crystal straight out of PF0/PF1 to the right, its load caps beside it
        ("Y401", M(5), B, out(5, right, 6)), ("C409", ("Y401", "1"), B, None), ("C410", ("Y401", "3"), B, None),
        ("C411", M(7), B, out(7, right)), ("R401", M(45), B, out(45, up)),
        # current-sense RC (cap at the ADC pin, 100 Ω toward the DRV's SOx), SPI source resistors, pull-ups
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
